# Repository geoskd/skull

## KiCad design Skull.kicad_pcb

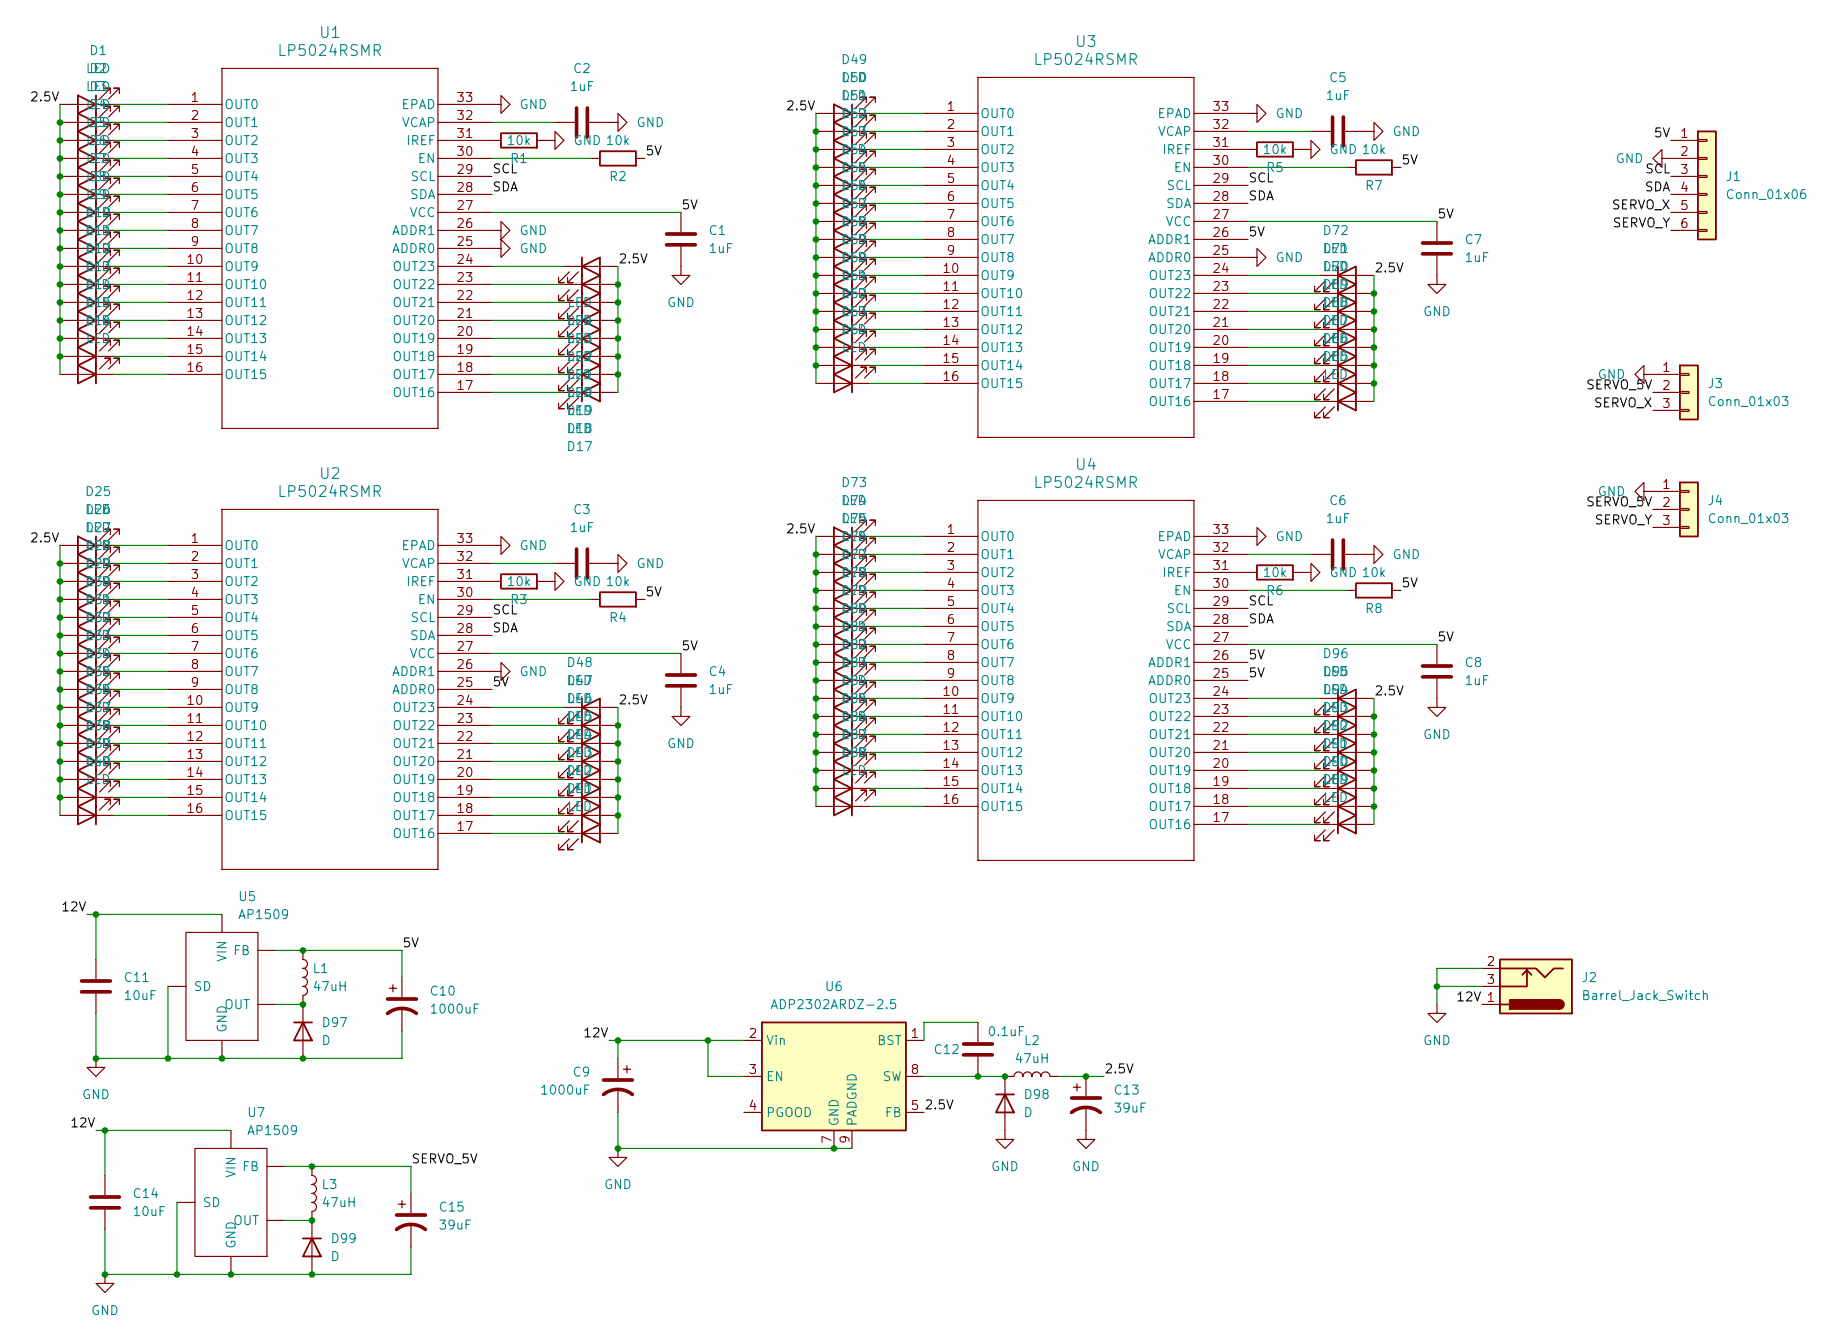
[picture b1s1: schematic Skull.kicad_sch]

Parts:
C1, C2, C3, C4, C5, C6, C7, C8: 1uF; C_0603_1608Metric
C9, C10: 1000uF; CP_Radial_D10.0mm_P5.00mm
C11, C14: 10uF; C_1206_3216Metric_Pad1.33x1.80mm_HandSolder
C12: 0.1uF; C_0603_1608Metric
C13, C15: 39uF; CP_Elec_6.3x5.9
D1, D2, D3, D4, D5, D6, D7, D8, D9, D10, D11, D12, D13, D14, D15, D16, D17, D18, D19, D20, D21, D22, D23, D24, D25, D26, D27, D28, D29, D30, D31, D32, D33, D34, D35, D36, D37, D38, D39, D40, D41, D42, D43, D44, D45, D46, D47, D48, D49, D50, D51, D52, D53, D54, D55, D56, D57, D58, D59, D60, D61, D62, D63, D64, D65, D66, D67, D68, D69, D70, D71, D72, D73, D74, D75, D76, D77, D78, D79, D80, D81, D82, D83, D84, D85, D86, D87, D88, D89, D90, D91, D92, D93, D94, D95, D96: LED; LED_0805_2012Metric
D97, D98, D99: D; D_SMA-SMB_Universal_Handsoldering
J1: Conn_01x06; PinHeader_2x03_P2.54mm_Vertical
J2: Barrel_Jack_Switch; BarrelJack_GCT_DCJ200-10-A_Horizontal
J3, J4: Conn_01x03; PinHeader_1x03_P2.54mm_Vertical
L1, L2, L3: 47uH; L_Bourns-SRN1060
R1, R2, R3, R4, R5, R6, R7, R8: 10k; R_0603_1608Metric
U1, U2, U3, U4: LP5024RSMR; QFN-32-1EP_4x4mm_P0.4mm_EP2.9x2.9mm
U5, U7: AP1509; SO-8_3.9x4.9mm_P1.27mm
U6: ADP2302ARDZ-2.5; SOIC-8-1EP_3.9x4.9mm_P1.27mm_EP2.29x3mm

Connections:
/2.5V: C13.1, D1.2 (A), D2.2 (A), D3.2 (A), D4.2 (A), D5.2 (A), D6.2 (A), D7.2 (A), D8.2 (A), D9.2 (A), D10.2 (A), D11.2 (A), D12.2 (A), D13.2 (A), D14.2 (A), D15.2 (A), D16.2 (A), D17.2 (A), D18.2 (A), D19.2 (A), D20.2 (A), D21.2 (A), D22.2 (A), D23.2 (A), D24.2 (A), D25.2 (A), D26.2 (A), D27.2 (A), D28.2 (A), D29.2 (A), D30.2 (A), D31.2 (A), D32.2 (A), D33.2 (A), D34.2 (A), D35.2 (A), D36.2 (A), D37.2 (A), D38.2 (A), D39.2 (A), D40.2 (A), D41.2 (A), D42.2 (A), D43.2 (A), D44.2 (A), D45.2 (A), D46.2 (A), D47.2 (A), D48.2 (A), D49.2 (A), D50.2 (A), D51.2 (A), D52.2 (A), D53.2 (A), D54.2 (A), D55.2 (A), D56.2 (A), D57.2 (A), D58.2 (A), D59.2 (A), D60.2 (A), D61.2 (A), D62.2 (A), D63.2 (A), D64.2 (A), D65.2 (A), D66.2 (A), D67.2 (A), D68.2 (A), D69.2 (A), D70.2 (A), D71.2 (A), D72.2 (A), D73.2 (A), D74.2 (A), D75.2 (A), D76.2 (A), D77.2 (A), D78.2 (A), D79.2 (A), D80.2 (A), D81.2 (A), D82.2 (A), D83.2 (A), D84.2 (A), D85.2 (A), D86.2 (A), D87.2 (A), D88.2 (A), D89.2 (A), D90.2 (A), D91.2 (A), D92.2 (A), D93.2 (A), D94.2 (A), D95.2 (A), D96.2 (A), L2.2, U6.5 (FB)
/5V: C1.1, C4.1, C7.1, C8.1, C10.1, J1.1, L1.1, R2.2, R4.2, R7.2, R8.2, U1.27 (VCC), U2.25 (ADDR0), U2.27 (VCC), U3.26 (ADDR1), U3.27 (VCC), U4.25 (ADDR0), U4.26 (ADDR1), U4.27 (VCC), U5.3 (FB)
/12V: C9.1, C11.1, C14.1, J2.1, U5.1 (VIN), U6.2 (Vin), U6.3 (EN), U7.1 (VIN)
/SCL: J1.3, U1.29 (SCL), U2.29 (SCL), U3.29 (SCL), U4.29 (SCL)
/SDA: J1.4, U1.28 (SDA), U2.28 (SDA), U3.28 (SDA), U4.28 (SDA)
/SERVO_5V: C15.1, J3.2, J4.2, L3.1, U7.3 (FB)
/SERVO_X: J1.5, J3.3
/SERVO_Y: J1.6, J4.3
GND: C1.2, C2.2, C3.2, C4.2, C5.2, C6.2, C7.2, C8.2, C9.2, C10.2, C11.2, C13.2, C14.2, C15.2, D97.2 (A), D98.2 (A), D99.2 (A), J1.2, J2.2, J2.3, J3.1, J4.1, R1.2, R3.2, R5.2, R6.2, U1.25 (ADDR0), U1.26 (ADDR1), U1.33 (EPAD), U2.26 (ADDR1), U2.33 (EPAD), U3.25 (ADDR0), U3.33 (EPAD), U4.33 (EPAD), U5.4 (SD), U5.5 (GND), U5.6 (GND), U5.7 (GND), U5.8 (GND), U6.7 (GND), U6.9 (PADGND), U7.4 (SD), U7.5 (GND), U7.6 (GND), U7.7 (GND), U7.8 (GND)
unnamed: D1.1 (K), U1.1 (OUT0)
unnamed: D2.1 (K), U1.2 (OUT1)
unnamed: D3.1 (K), U1.3 (OUT2)
unnamed: D4.1 (K), U1.4 (OUT3)
unnamed: D5.1 (K), U1.5 (OUT4)
unnamed: D6.1 (K), U1.6 (OUT5)
unnamed: D7.1 (K), U1.7 (OUT6)
unnamed: D8.1 (K), U1.8 (OUT7)
unnamed: D9.1 (K), U1.9 (OUT8)
unnamed: D10.1 (K), U1.10 (OUT9)
unnamed: D11.1 (K), U1.11 (OUT10)
unnamed: D12.1 (K), U1.12 (OUT11)
unnamed: D13.1 (K), U1.13 (OUT12)
unnamed: D14.1 (K), U1.14 (OUT13)
unnamed: D15.1 (K), U1.15 (OUT14)
unnamed: D16.1 (K), U1.16 (OUT15)
unnamed: D17.1 (K), U1.17 (OUT16)
unnamed: D18.1 (K), U1.18 (OUT17)
unnamed: D19.1 (K), U1.19 (OUT18)
unnamed: D20.1 (K), U1.20 (OUT19)
unnamed: D21.1 (K), U1.21 (OUT20)
unnamed: D22.1 (K), U1.22 (OUT21)
unnamed: D23.1 (K), U1.23 (OUT22)
unnamed: D24.1 (K), U1.24 (OUT23)
unnamed: D25.1 (K), U2.1 (OUT0)
unnamed: D26.1 (K), U2.2 (OUT1)
unnamed: D27.1 (K), U2.3 (OUT2)
unnamed: D28.1 (K), U2.4 (OUT3)
unnamed: D29.1 (K), U2.5 (OUT4)
unnamed: D30.1 (K), U2.6 (OUT5)
unnamed: D31.1 (K), U2.7 (OUT6)
unnamed: D32.1 (K), U2.8 (OUT7)
unnamed: D33.1 (K), U2.9 (OUT8)
unnamed: D34.1 (K), U2.10 (OUT9)
unnamed: D35.1 (K), U2.11 (OUT10)
unnamed: D36.1 (K), U2.12 (OUT11)
unnamed: D37.1 (K), U2.13 (OUT12)
unnamed: D38.1 (K), U2.14 (OUT13)
unnamed: D39.1 (K), U2.15 (OUT14)
unnamed: D40.1 (K), U2.16 (OUT15)
unnamed: D41.1 (K), U2.17 (OUT16)
unnamed: D42.1 (K), U2.18 (OUT17)
unnamed: D43.1 (K), U2.19 (OUT18)
unnamed: D44.1 (K), U2.20 (OUT19)
unnamed: D45.1 (K), U2.21 (OUT20)
unnamed: D46.1 (K), U2.22 (OUT21)
unnamed: D47.1 (K), U2.23 (OUT22)
unnamed: D48.1 (K), U2.24 (OUT23)
unnamed: D49.1 (K), U3.1 (OUT0)
unnamed: D50.1 (K), U3.2 (OUT1)
unnamed: D51.1 (K), U3.3 (OUT2)
unnamed: D52.1 (K), U3.4 (OUT3)
unnamed: D53.1 (K), U3.5 (OUT4)
unnamed: D54.1 (K), U3.6 (OUT5)
unnamed: D55.1 (K), U3.7 (OUT6)
unnamed: D56.1 (K), U3.8 (OUT7)
unnamed: D57.1 (K), U3.9 (OUT8)
unnamed: D58.1 (K), U3.10 (OUT9)
unnamed: D59.1 (K), U3.11 (OUT10)
unnamed: D60.1 (K), U3.12 (OUT11)
unnamed: D61.1 (K), U3.13 (OUT12)
unnamed: D62.1 (K), U3.14 (OUT13)
unnamed: D63.1 (K), U3.15 (OUT14)
unnamed: D64.1 (K), U3.16 (OUT15)
unnamed: D65.1 (K), U3.17 (OUT16)
unnamed: D66.1 (K), U3.18 (OUT17)
unnamed: D67.1 (K), U3.19 (OUT18)
unnamed: D68.1 (K), U3.20 (OUT19)
unnamed: D69.1 (K), U3.21 (OUT20)
unnamed: D70.1 (K), U3.22 (OUT21)
unnamed: D71.1 (K), U3.23 (OUT22)
unnamed: D72.1 (K), U3.24 (OUT23)
unnamed: D73.1 (K), U4.1 (OUT0)
unnamed: D74.1 (K), U4.2 (OUT1)
unnamed: D75.1 (K), U4.3 (OUT2)
unnamed: D76.1 (K), U4.4 (OUT3)
unnamed: D77.1 (K), U4.5 (OUT4)
unnamed: D78.1 (K), U4.6 (OUT5)
unnamed: D79.1 (K), U4.7 (OUT6)
unnamed: D80.1 (K), U4.8 (OUT7)
unnamed: D81.1 (K), U4.9 (OUT8)
unnamed: D82.1 (K), U4.10 (OUT9)
unnamed: D83.1 (K), U4.11 (OUT10)
unnamed: D84.1 (K), U4.12 (OUT11)
unnamed: D85.1 (K), U4.13 (OUT12)
unnamed: D86.1 (K), U4.14 (OUT13)
unnamed: D87.1 (K), U4.15 (OUT14)
unnamed: D88.1 (K), U4.16 (OUT15)
unnamed: D89.1 (K), U4.17 (OUT16)
unnamed: D90.1 (K), U4.18 (OUT17)
unnamed: D91.1 (K), U4.19 (OUT18)
unnamed: D92.1 (K), U4.20 (OUT19)
unnamed: D93.1 (K), U4.21 (OUT20)
unnamed: D94.1 (K), U4.22 (OUT21)
unnamed: D95.1 (K), U4.23 (OUT22)
unnamed: D96.1 (K), U4.24 (OUT23)
unnamed: D97.1 (K), L1.2, U5.2 (OUT)
unnamed: C12.1, D98.1 (K), L2.1, U6.8 (SW)
unnamed: D99.1 (K), L3.2, U7.2 (OUT)
unnamed: R2.1, U1.30 (EN)
unnamed: R1.1, U1.31 (IREF)
unnamed: C2.1, U1.32 (VCAP)
unnamed: R4.1, U2.30 (EN)
unnamed: R3.1, U2.31 (IREF)
unnamed: C3.1, U2.32 (VCAP)
unnamed: R7.1, U3.30 (EN)
unnamed: R5.1, U3.31 (IREF)
unnamed: C5.1, U3.32 (VCAP)
unnamed: R8.1, U4.30 (EN)
unnamed: R6.1, U4.31 (IREF)
unnamed: C6.1, U4.32 (VCAP)
unnamed: C12.2, U6.1 (BST)

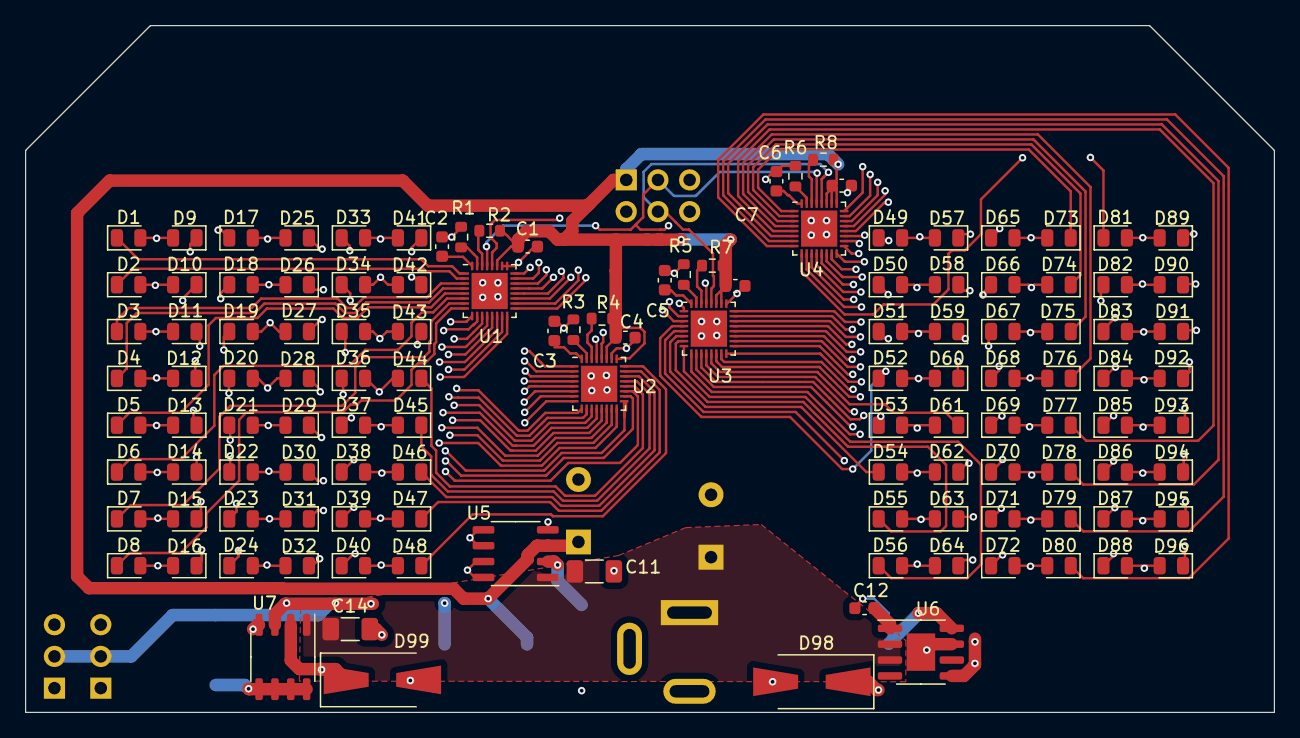
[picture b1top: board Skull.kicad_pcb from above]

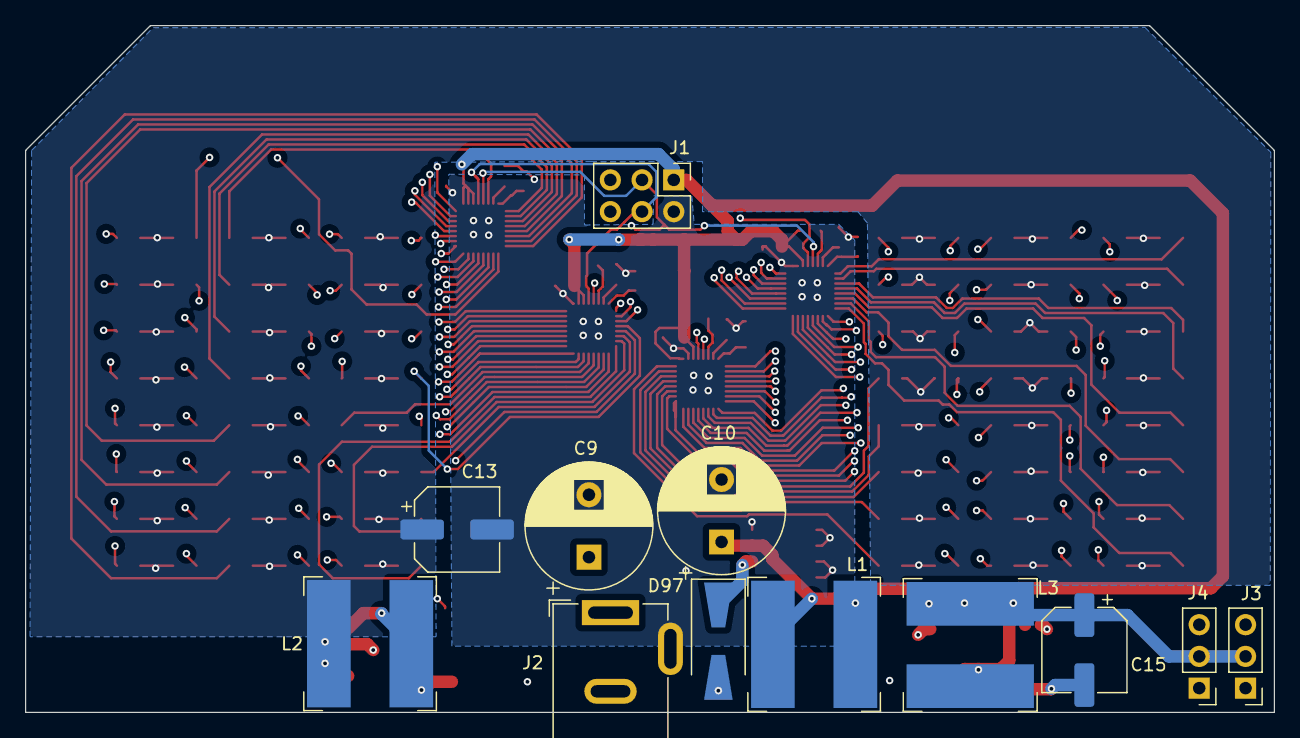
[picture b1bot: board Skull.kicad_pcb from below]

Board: 4 copper layers, 100.0 x 55.0 mm, 136 parts (12 on the bottom side), 121 nets.

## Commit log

2024-09-22 loaded working code from device
